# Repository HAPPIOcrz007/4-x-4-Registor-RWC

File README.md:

# 4×4 Register PCB — Read / Write / Asynchronous Clear

A first-year B.Tech Digital Electronics project implementing a **4×4 register file** using standard 74-series TTL ICs, progressing from Logisim simulation through breadboard prototyping to a fabricated KiCad PCB — verified live at the **Circuit Conclave Hackathon 2026, MIT World Peace University**.

> 🏅 **Recommended by the Department Head and leading faculty of the Department of Electrical & Electronics Engineering, MIT-WPU, as a future laboratory teaching kit** — recognised for its compact 15×15 cm form factor, intuitive layout, and pedagogical value for FY B.Tech students.

---

## ✨ Features

- **4 registers × 4 bits each** — 16 bits total volatile storage
- **2-bit address bus** for row selection via SN74LS139AN decoder
- **Synchronous write** — data latched on rising edge of NE555P astable clock (0.5 Hz)
- **Tri-state buffered read** — selected register drives shared LED output bus via SN74LS244N
- **Asynchronous clear** — active-low reset of addressed register, independent of clock
- **Single RW push-button** for mode control (default = read, pressed = write)
- **4 output LEDs** (CQY99) displaying bus values in real time
- **Compact 15×15 cm PCB** — all 31 components placed and routed on a 2-layer board
- **Single +5V supply** (see Hardware Notes for 6V field experience)

---

## 🏆 Presented At

**Circuit Conclave Hackathon 2026**
DoEEE & prismlabs Student Club | MIT World Peace University, Pune
FY B.Tech E&CE — Division 23 | Academic Year 2025–26

The PCB was demonstrated live before a jury comprising faculty from Basic Electrical Engineering, Digital Electronics, and an external industry examiner. The board powered up cleanly and passed all functional tests on the day — write, read, hold, and clear verified across all four register addresses.

**The project received special recognition from the Department Head and senior faculty of the DoEEE, who recommended it be adopted as a hands-on laboratory teaching kit for future first-year batches.**

### Team
| Member | Role |
|--------|-----|
| Harshvardhan M Rathod | Pcb Design, Logical iterations, connections, development, verifications and ordering |
| Alok Deep Verma | report and ppt writing and printing |

**Faculty Mentor:** Dr. Sarika Patil &nbsp;|&nbsp; **Digital Electronics:** Dr. Manisha Ingle

---

## 📂 Repository Structure

```
.
├── 4X4_MEMORY_READ_WRITE.circ           # Logisim Evolution simulation file
├── BOM.pdf                              # Bill of Materials (KiCad export)
├── Component box/                       # Custom component libraries
│   ├── <IC or switch folders>/          #   KiCad symbols, footprints, STEP models
│   └── License.txt
├── KiKad/                               # KiCad project files
│   ├── 4-x-4-Registor-RWC.kicad_pcb    #   PCB layout
│   ├── 4-x-4-Registor-RWC.kicad_sch    #   Schematic
│   ├── 4-x-4-Registor-RWC.kicad_pro    #   Project file
│   ├── 4-x-4-Registor-RWC.kicad_prl    #   Project local settings
│   └── 4-x-4-Registor-RWC.pretty/      #   Custom footprints
├── RAM-project-001.csv                  # Raw BOM CSV export
├── Report.pdf                           # Full project report
├── sm_black_top.png                     # PCB render — top view (KiCad)
├── output.pdf                           # schematic drawing sheet pdf
├── pcb_output.pdf                       # pcb order copy pdf
└── README.md                            # This file
```

---

## 📦 Bill of Materials

**Total: 31 components | 2-layer PCB | Single +5V supply**

| Category | Qty | Key Parts |
|----------|-----|-----------|
| ICs | 11 | SN74LS175N ×4, SN74LS139AN, SN74LS244N ×2, SN74LS08N, SN7402N, SN7432N, NE555P |
| Switches | 8 | SPST inputs (D0–D3, A0–A1), RW push-button, Clear push-button |
| LEDs | 4 | CQY99 — output bus indicators (Bits 0–3) |
| Resistors | 6 | 220 Ω ×4 (LED limiting), 10 kΩ + 68 kΩ (NE555P timing network) |
| Capacitors | 2 | 0.1 µF ceramic disc — VCC decoupling |
| **Total** | **31** | — |

---

## ⚙️ Operating Modes

| Mode | RW (SWW1) | Address | Clock | CLR\ | Result |
|------|-----------|---------|-------|------|--------|
| Write | 1 — pressed | Row n | ↑ rising edge | 1 | Data latched into Row n |
| Read | 0 — default | Row n | — | 1 | Row n displayed on OL0–OL3 |
| Hold | 0 | Any | — | 1 | No change |
| Clear | X | Row n | — | 0 — pressed | Selected row reset to 0000 |

**Clock frequency:** `f = 1.44 / [(R1 + 2×R2) × C] = 1.44 / [146 kΩ × 20 µF] ≈ 0.5 Hz`

---

## 🔧 Hardware Notes & Lessons Learned

### Power Supply — 6V Field Operation
The board was designed for a regulated **+5V** supply. During the live demonstration it was powered from a **6V battery**, with a **toggle switch inserted between the battery and the VCC patch point** for clean power-on/off control. The 74LS-series ICs functioned correctly at 6V for the duration of the demo. Note that 6V is outside the 74LS absolute maximum rating (5V ±5%), so a regulated 5V supply (e.g. 7805 linear regulator or USB power module) is recommended for sustained operation.

### Noise on SN74LS175N — Decoupling Lesson
During live testing, switching noise was observed being picked up on the **SN74LS175N (Quad D Flip-Flop) VCC pins**, occasionally causing spurious state changes on the output. The examining faculty identified the root cause immediately:

**Fix recommended by faculty:**
> Add a **0.1 µF ceramic capacitor between VCC and GND at every IC's power pins**, placed as physically close to each DIP package as possible.

The existing BOM includes two 0.1 µF decoupling caps (CC1, CC2). The lesson: **every IC in a TTL design should have its own dedicated decoupling capacitor** — not just selected ICs. Switching transients from multiple ICs sharing the same power rail accumulate and cause exactly this noise behaviour.

**Updated decoupling plan for next PCB revision:**

| IC | KiCad Ref | Decoupling Cap |
|----|-----------|----------------|
| SN74LS175N ×4 | D074175–D374175 | 0.1 µF per IC — **×4 to add** |
| SN74LS139AN | D74139 | 0.1 µF — **to add** |
| SN74LS08N | A7408 | 0.1 µF — **to add** |
| SN7402N | N7402 | 0.1 µF — **to add** |
| SN7432N | O7432 | 0.1 µF — **to add** |
| NE555P | CNE555 | 0.1 µF — **to add** |
| SN74LS244N ×2 | B074244, B174244 | 0.1 µF — already placed ✓ |

**Total additional caps for Rev 2: +7 × 0.1 µF ceramic disc**

---

## 🖥️ Simulation

The full register file was first verified in **Logisim Evolution** (`4X4_MEMORY_READ_WRITE.circ`) before any hardware was built. All four operating modes — write, read, hold, and clear — were confirmed across all four register addresses in simulation before committing to PCB layout.

---

## 📚 References

- Texas Instruments datasheets: [SN74LS175](https://www.ti.com/lit/gpn/sn74ls175) · [SN74LS139A](https://www.ti.com/lit/gpn/sn74ls139a) · [SN74LS244](https://www.ti.com/lit/gpn/sn74ls244) · [NE555](https://www.ti.com/lit/gpn/ne555)
- M. M. Mano & M. D. Ciletti, *Digital Design*, 5th ed., Pearson
- D. A. Patterson & J. L. Hennessy, *Computer Organisation and Design*, 5th ed., Morgan Kaufmann

---

## 🚀 Future Work

- Add 0.1 µF decoupling capacitor at each IC VCC pin (see Hardware Notes above)
- On-board 7805 / LDO regulator footprint for regulated 5V from a 9V battery
- Expansion connector for 16-LED monitor matrix (as in Logisim simulation)
- FPGA / HDL implementation for direct speed and area comparison
- Formal adoption as DoEEE laboratory teaching kit for future FY B.Tech batches

---

## 📜 License

- **Hardware design files:** CERN OHL v2 (Strongly Reciprocal)
- **Code & documentation:** MIT License

See `LICENSE` for full terms.

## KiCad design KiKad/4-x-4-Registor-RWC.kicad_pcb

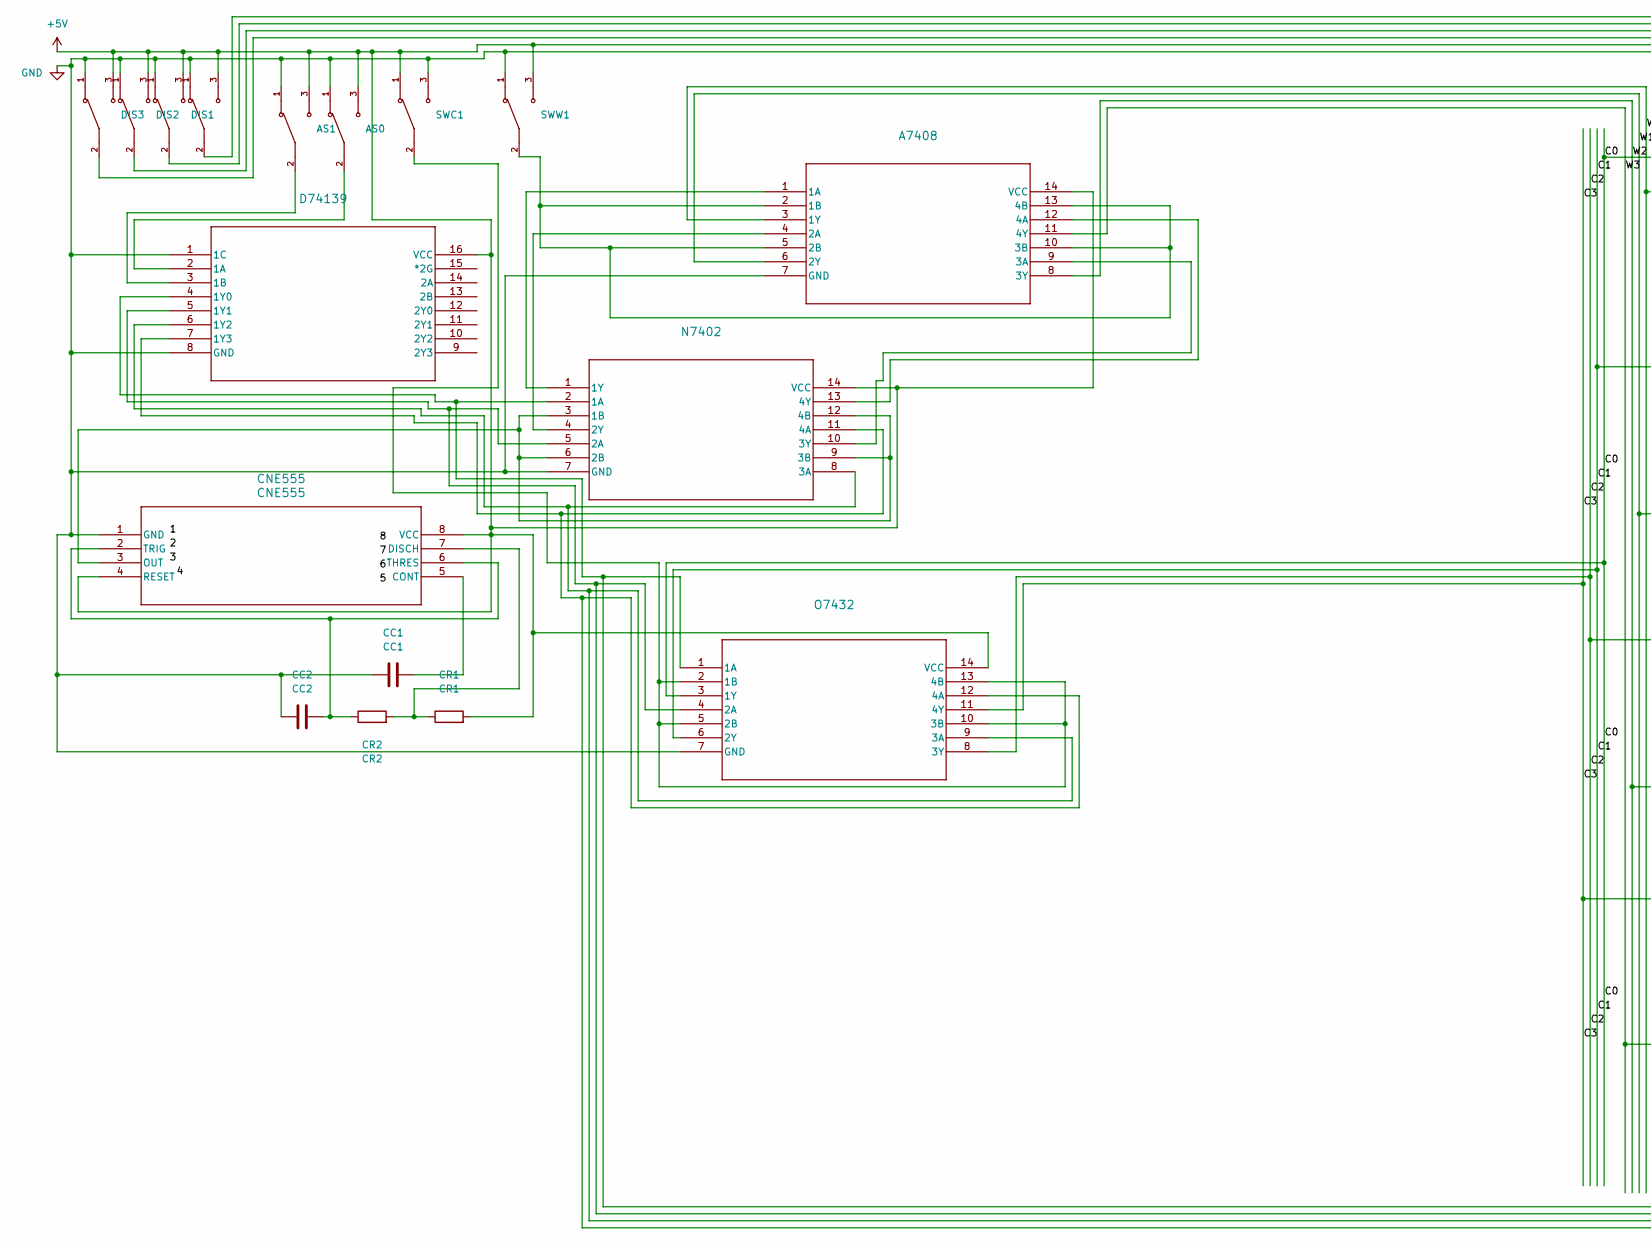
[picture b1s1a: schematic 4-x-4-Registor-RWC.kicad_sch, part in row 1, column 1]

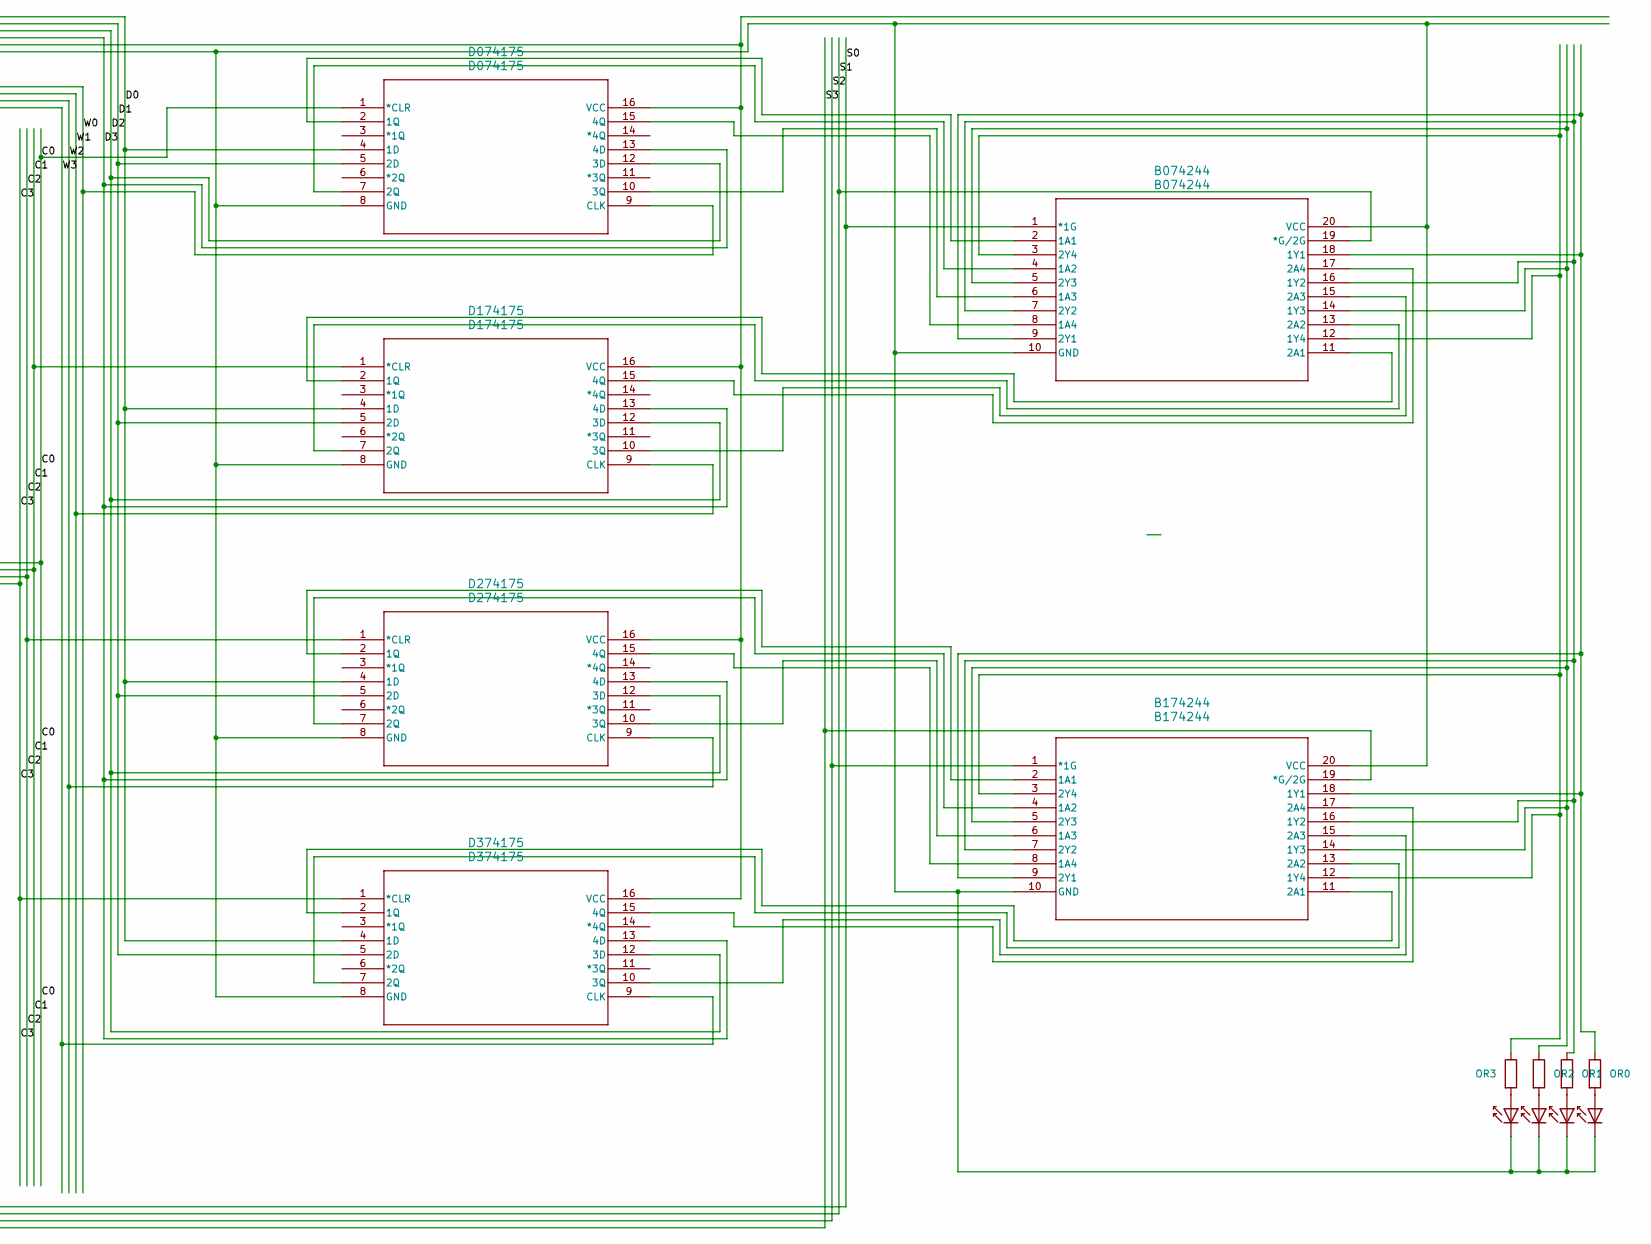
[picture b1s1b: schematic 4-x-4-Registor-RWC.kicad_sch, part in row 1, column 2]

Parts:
A7408: A7408; SN74LS08N
AS0: AS0; SW_100SP1T1B4M2QE; PARTREV E
AS1: AS1; SW_100SP1T1B4M2QE; PARTREV E
B074244: B074244; SN74LS244N
B174244: B174244; SN74LS244N
CC1: CC1; C_Disc_D5.0mm_W2.5mm_P5.00mm
CC2: CC2; C_Disc_D5.0mm_W2.5mm_P5.00mm
CNE555: CNE555; NE555P
CR1: CR1; R_Axial_DIN0207_L6.3mm_D2.5mm_P10.16mm_Horizontal
CR2: CR2; R_Axial_DIN0207_L6.3mm_D2.5mm_P10.16mm_Horizontal
D74139: D74139; SN74LS139AN
D074175: D074175; SN74LS175N
D174175: D174175; SN74LS175N
D274175: D274175; SN74LS175N
D374175: D374175; SN74LS175N
DIS0: DIS0; SW_100SP1T1B4M2QE; PARTREV E
DIS1: DIS1; SW_100SP1T1B4M2QE; PARTREV E
DIS2: DIS2; SW_100SP1T1B4M2QE; PARTREV E
DIS3: DIS3; SW_100SP1T1B4M2QE; PARTREV E
N7402: N7402; SN7402N
O7432: O7432; SN7432N
OL0, OL1, OL2, OL3: CQY99; LED_D5.0mm
OR0, OR1, OR2, OR3: R; R_Axial_DIN0207_L6.3mm_D2.5mm_P10.16mm_Horizontal
SWC1: SWC; SW_100SP1T1B4M2QE; PARTREV E
SWW1: SWW; SW_100SP1T1B4M2QE; PARTREV E

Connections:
/C0: D074175.1 (*CLR), O7432.3 (1Y)
/C1: D174175.1 (*CLR), O7432.6 (2Y)
/C2: D274175.1 (*CLR), O7432.8 (3Y)
/C3: D374175.1 (*CLR), O7432.11 (4Y)
/D0: D074175.4 (1D), D174175.4 (1D), D274175.4 (1D), D374175.4 (1D), DIS0.2
/D1: D074175.5 (2D), D174175.5 (2D), D274175.5 (2D), D374175.5 (2D), DIS1.2
/D2: D074175.12 (3D), D174175.12 (3D), D274175.12 (3D), D374175.12 (3D), DIS2.2
/D3: D074175.13 (4D), D174175.13 (4D), D274175.13 (4D), D374175.13 (4D), DIS3.2
/S0: B074244.1 (*1G), D74139.4 (1Y0), N7402.2 (1A), O7432.1 (1A)
/S1: B074244.19 (*G/2G), D74139.5 (1Y1), N7402.5 (2A), O7432.4 (2A)
/S2: B174244.1 (*1G), D74139.6 (1Y2), N7402.8 (3A), O7432.9 (3A)
/S3: B174244.19 (*G/2G), D74139.7 (1Y3), N7402.11 (4A), O7432.12 (4A)
/W0: A7408.3 (1Y), D074175.9 (CLK)
/W1: A7408.6 (2Y), D174175.9 (CLK)
/W2: A7408.8 (3Y), D274175.9 (CLK)
/W3: A7408.11 (4Y), D374175.9 (CLK)
unnamed: A7408.1 (1A), N7402.1 (1Y)
unnamed: A7408.2 (1B), A7408.5 (2B), A7408.10 (3B), A7408.13 (4B), SWW1.2
unnamed: A7408.4 (2A), N7402.4 (2Y)
unnamed: A7408.9 (3A), N7402.10 (3Y)
unnamed: A7408.12 (4A), N7402.13 (4Y)
unnamed: B074244.2 (1A1), D074175.2 (1Q)
unnamed: B074244.4 (1A2), D074175.7 (2Q)
unnamed: B074244.6 (1A3), D074175.10 (3Q)
unnamed: B074244.8 (1A4), D074175.15 (4Q)
unnamed: B074244.9 (2Y1), B074244.18 (1Y1), B174244.9 (2Y1), B174244.18 (1Y1), OR0.1
unnamed: B074244.7 (2Y2), B074244.16 (1Y2), B174244.7 (2Y2), B174244.16 (1Y2), OR1.1
unnamed: B074244.5 (2Y3), B074244.14 (1Y3), B174244.5 (2Y3), B174244.14 (1Y3), OR2.1
unnamed: B074244.3 (2Y4), B074244.12 (1Y4), B174244.3 (2Y4), B174244.12 (1Y4), OR3.1
unnamed: B074244.11 (2A1), D174175.2 (1Q)
unnamed: B074244.13 (2A2), D174175.7 (2Q)
unnamed: B074244.15 (2A3), D174175.10 (3Q)
unnamed: B074244.17 (2A4), D174175.15 (4Q)
unnamed: B174244.2 (1A1), D274175.2 (1Q)
unnamed: B174244.4 (1A2), D274175.7 (2Q)
unnamed: B174244.6 (1A3), D274175.10 (3Q)
unnamed: B174244.8 (1A4), D274175.15 (4Q)
unnamed: B174244.11 (2A1), D374175.2 (1Q)
unnamed: B174244.13 (2A2), D374175.7 (2Q)
unnamed: B174244.15 (2A3), D374175.10 (3Q)
unnamed: B174244.17 (2A4), D374175.15 (4Q)
unnamed: CC1.2, CNE555.5 (CONT)
unnamed: CNE555.7 (DISCH), CR1.1, CR2.2
unnamed: CNE555.3 (OUT), N7402.3 (1B), N7402.6 (2B), N7402.9 (3B), N7402.12 (4B)
unnamed: CC2.2, CNE555.2 (TRIG), CNE555.6 (THRES), CR2.1
unnamed: AS0.2, D74139.2 (1A)
unnamed: AS1.2, D74139.3 (1B)
unnamed: O7432.2 (1B), O7432.5 (2B), O7432.10 (3B), O7432.13 (4B), SWC1.2
unnamed: OL0.2 (A), OR0.2
unnamed: OL1.2 (A), OR1.2
unnamed: OL2.2 (A), OR2.2
unnamed: OL3.2 (A), OR3.2

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
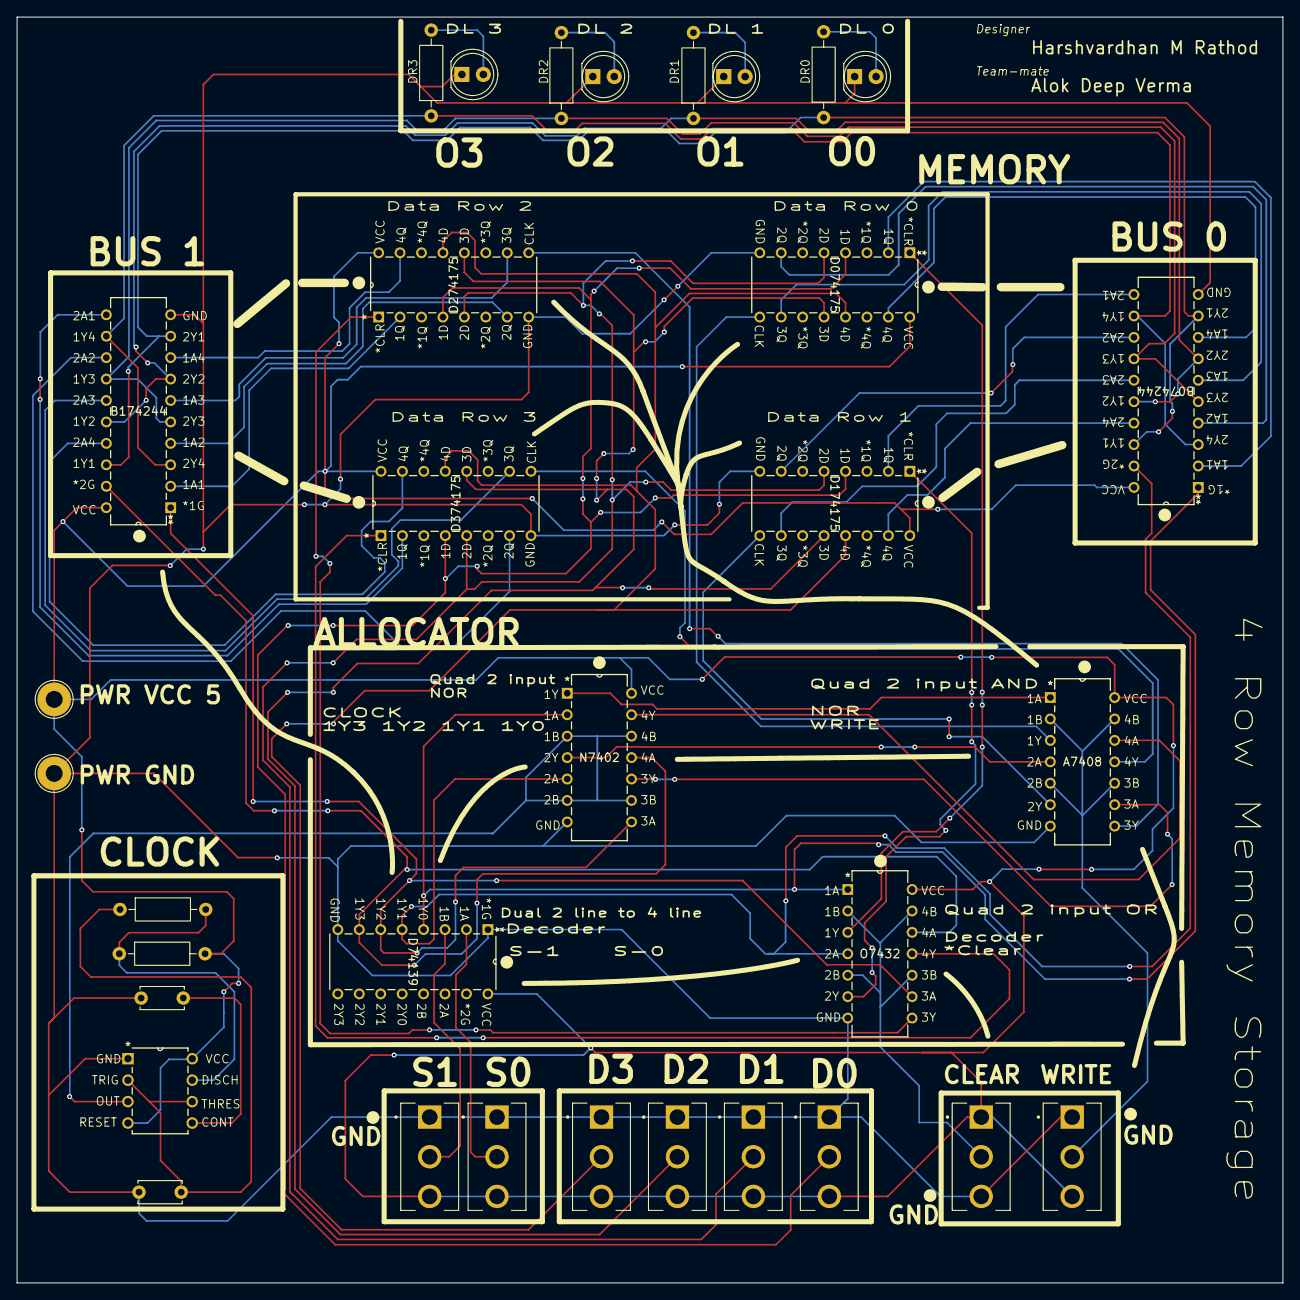
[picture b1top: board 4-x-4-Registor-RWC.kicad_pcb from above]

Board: 2 copper layers, 150.0 x 150.0 mm, 32 parts (0 on the bottom side), 54 nets.

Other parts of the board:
PWR GND: TestPoint_THTPad_D4.0mm_Drill2.0mm

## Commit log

2026-04-01 updated files
2026-04-22 files updated Finalised
2026-04-22 update final
